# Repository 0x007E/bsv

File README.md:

# `BSV` - (Bluetooth) Stereo Amplifier (Stereoverstärker)

The `BSV` project is based on a pcb with a transistor amplifier. It can be combined with a [Bluetooth audio module](https://eu.robotshop.com/de/products/bluetooth-50-audio-receiver-board) or with an audio jack only.

| Experience | Level |
|:------------|:-----:|
| Soldering   |  |
| Mechanical  |  |

# Downloads

| Type      | File               | Description              |
|:---------:|:------------------:|:-------------------------|
| Lochmaster | [lm4](https://github.com/0x007E/bsv/raw/refs/heads/main/BSV.LM4) | Stripe grid circuit board | 
| Schematic | [pdf](https://github.com/0x007E/bsv/releases/latest/download/schematic.pdf) / [cadlab](https://cadlab.io/project/28570/main/files)     | Schematic files          |
| Board     | [pdf](https://github.com/0x007E/bsv/releases/latest/download/pcb.pdf) / [cadlab](https://cadlab.io/project/28570/main/files)     | Board file               |
| Drill     | [pdf](https://github.com/0x007E/bsv/releases/latest/download/drill.pdf) | Drill file               |
| Gerber    | [zip](https://github.com/0x007E/bsv/releases/latest/download/kicad.zip) / [tar](https://github.com/0x007E/bsv/releases/latest/download/kicad.tar.gz)                | Gerber/Drill files       |
| Housing, PCB | [zip](https://github.com/0x007E/bsv/releases/latest/download/freecad.zip) / [tar](https://github.com/0x007E/bsv/releases/latest/download/freecad.tar.gz) | Housing and PCB (STEP) files     |

# Hardware

There are two parts of the hardware. The pcb and the housing of the `BSV`. The pcb is created with `KiCAD` and the housing with `FreeCAD`. All files are built with `github actions` so that they are ready for a production environment. The housing is printed with a 3D-printer (`Dremel 3D40`).

## PCB

The circuit board is populated on one side (Top). The best way for soldering is within a standard soldering system.

### Top Layer

### Bottom Layer

## Mechanical

The housing has a tolerance of `0.2mm` on each side of the case. So the pcb should fit perfectly in the housing. The tolerance can be modified with `FreeCAD` in the `Parameter` Spreadsheet.

### Assembled

#### Exploded

# Additional Information

| Type       | Link               | Description              |
|:----------:|:------------------:|:-------------------------|
| BC547 | [pdf](https://www.sparkfun.com/datasheets/Components/BC546.pdf) | NPN 
| BC327 | [pdf](https://www.onsemi.com/pdf/datasheet/bc327-d.pdf) | NPN 
| BC337 | [pdf](https://www.onsemi.cn/download/data-sheet/pdf/bc337-fsc-d.pdf) | PNP Transistor |

---

R. GAECHTER

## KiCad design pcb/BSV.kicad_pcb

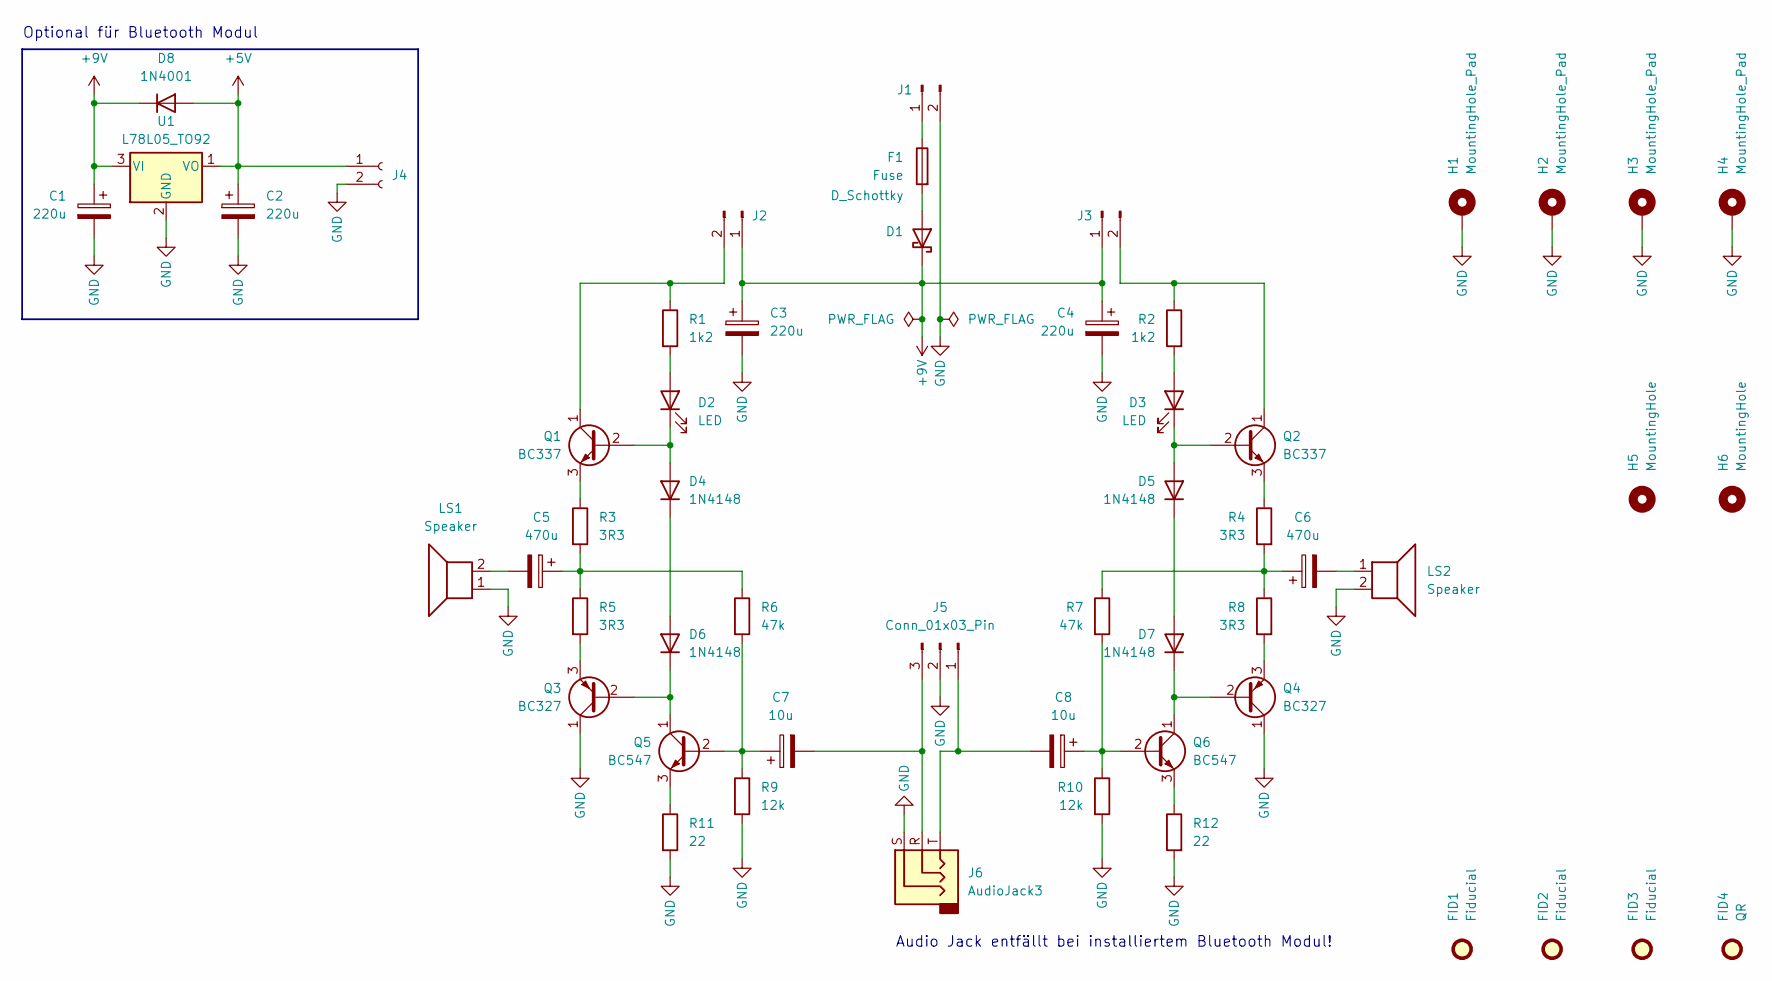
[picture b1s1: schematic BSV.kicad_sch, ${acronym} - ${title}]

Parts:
C1, C2: 220u; C_Radial_D6.3mm_H5.0mm_P2.50mm
C3, C4: 220u; CP_Radial_D8.0mm_P3.50mm
C5, C6: 470u; CP_Radial_D8.0mm_P3.50mm
C7, C8: 10u; CP_Radial_D5.0mm_P2.00mm
D1: D_Schottky; D_T-1_P10.16mm_Horizontal
D2, D3: LED; LED_D5.0mm
D4, D5, D6, D7: 1N4148; D_T-1_P10.16mm_Horizontal
D8: 1N4001; D_DO-41_SOD81_P10.16mm_Horizontal
F1: Fuse; Fuseholder_Clip-5x20mm_Littelfuse_111_Inline_P20.00x5.00mm_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
FID1: Fiducial; ESD-Logo_6.6x6mm_SilkScreen
FID2: Fiducial; OSHW-Logo2_7.3x6mm_SilkScreen
FID3: Fiducial; WEEE-Logo_4.2x6mm_SilkScreen
FID4: QR; QR_0x007e
H1, H2, H3, H4: MountingHole_Pad; MountingHole_3.2mm_M3_DIN965_Pad
H5, H6: MountingHole; MountingHole_3.2mm_M3
J1, J2, J3: Conn_01x02_Pin; PinHeader_1x02_P2.54mm_Vertical
J4: Conn_01x02_Socket; PinSocket_2x01_P2.54mm_Vertical
J5: Conn_01x03_Pin; PinHeader_1x03_P2.54mm_Vertical
J6: AudioJack3; Jack_3.5mm_CUI_SJ1-3533NG_Horizontal
LS1, LS2: Speaker; TerminalBlock_bornier-2_P5.08mm
Q1, Q2: BC337; TO-92_Wide
Q3, Q4: BC327; TO-92_Wide
Q5, Q6: BC547; TO-92_Wide
R1, R2: 1k2; R_Axial_DIN0207_L6.3mm_D2.5mm_P10.16mm_Horizontal
R3, R4, R5, R8: 3R3; R_Axial_DIN0207_L6.3mm_D2.5mm_P10.16mm_Horizontal
R6, R7: 47k; R_Axial_DIN0207_L6.3mm_D2.5mm_P10.16mm_Horizontal
R9, R10: 12k; R_Axial_DIN0207_L6.3mm_D2.5mm_P10.16mm_Horizontal
R11, R12: 22; R_Axial_DIN0207_L6.3mm_D2.5mm_P10.16mm_Horizontal
U1: L78L05_TO92; TO-92L_Wide

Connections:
+5V: C2.1, D8.2 (A), J4.1, U1.1 (VO)
+9V: C1.1, C3.1, C4.1, D1.1 (K), D8.1 (K), J2.1, J3.1, U1.3 (VI)
GND: C1.2, C2.2, C3.2, C4.2, H1.1, H2.1, H3.1, H4.1, J1.2, J4.2, J5.2, J6.S, LS1.1, LS2.2, Q3.1 (C), Q4.1 (C), R9.2, R10.2, R11.2, R12.2, U1.2 (GND)
unnamed: C5.1, R3.2, R5.1, R6.1
unnamed: C5.2, LS1.2
unnamed: C6.1, R4.2, R7.1, R8.1
unnamed: C6.2, LS2.1
unnamed: D1.2 (A), F1.2
unnamed: D2.2 (A), R1.2
unnamed: D2.1 (K), D4.2 (A), Q1.2 (B)
unnamed: D3.2 (A), R2.2
unnamed: D3.1 (K), D5.2 (A), Q2.2 (B)
unnamed: D4.1 (K), D6.2 (A)
unnamed: D5.1 (K), D7.2 (A)
unnamed: D6.1 (K), Q3.2 (B), Q5.1 (C)
unnamed: D7.1 (K), Q4.2 (B), Q6.1 (C)
unnamed: F1.1, J1.1
unnamed: J2.2, Q1.1 (C), R1.1
unnamed: J3.2, Q2.1 (C), R2.1
unnamed: C8.2, J5.1, J6.T
unnamed: C7.2, J5.3, J6.R
unnamed: Q1.3 (E), R3.1
unnamed: Q2.3 (E), R4.1
unnamed: Q3.3 (E), R5.2
unnamed: Q4.3 (E), R8.2
unnamed: C7.1, Q5.2 (B), R6.2, R9.1
unnamed: Q5.3 (E), R11.1
unnamed: C8.1, Q6.2 (B), R7.2, R10.1
unnamed: Q6.3 (E), R12.1

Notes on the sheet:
Audio Jack entfällt bei installiertem Bluetooth Modul!
Optional für Bluetooth Modul

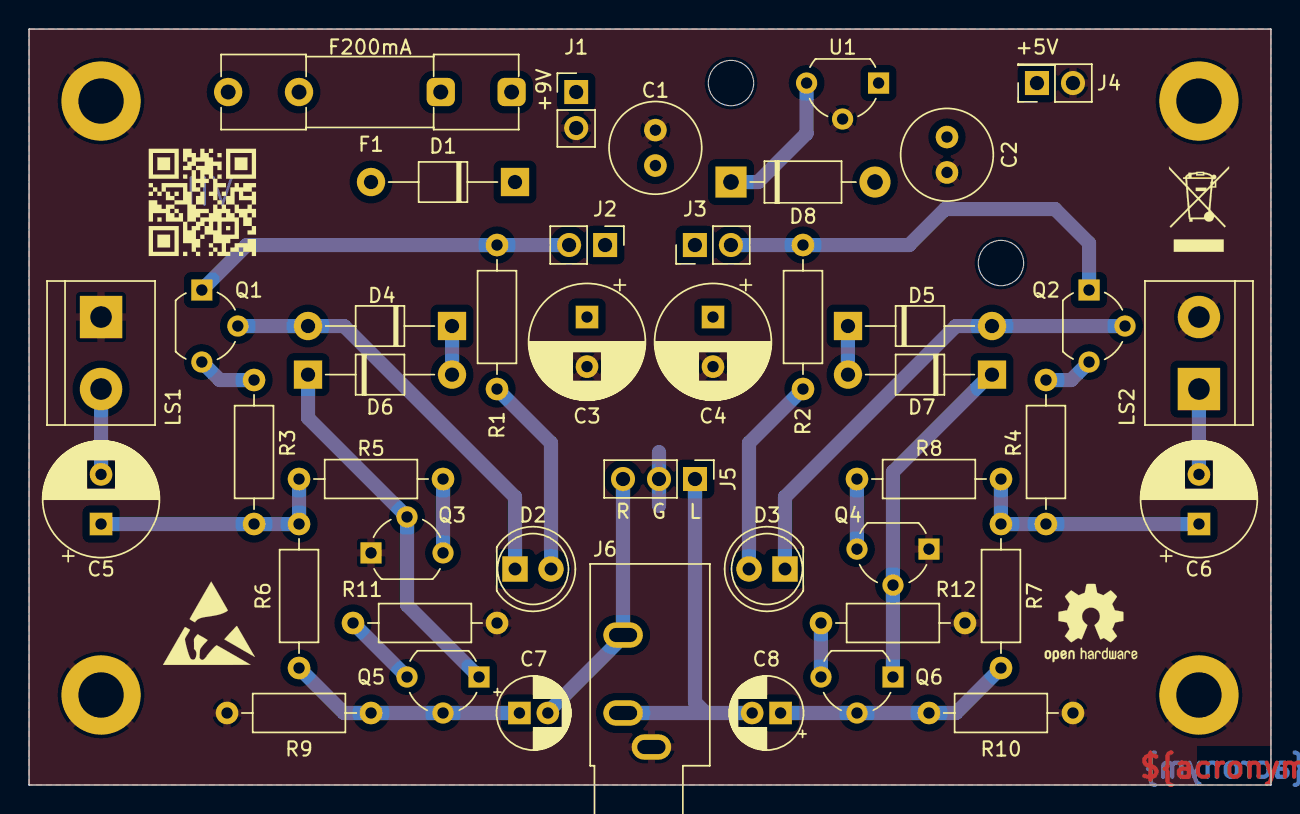
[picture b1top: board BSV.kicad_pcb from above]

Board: 2 copper layers, 87.6 x 53.3 mm, 54 parts (0 on the bottom side), 29 nets.

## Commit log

2024-10-16 Add README
2024-10-16 Create pipeline
2024-10-16 Fix e/drc filter
2024-10-16 Adapt PCB variables
2024-10-18 Fix typo

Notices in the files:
README.md:
License CC By-NC-SA
parts and their libraries:
license: CC BY-NC-SA 4.0
